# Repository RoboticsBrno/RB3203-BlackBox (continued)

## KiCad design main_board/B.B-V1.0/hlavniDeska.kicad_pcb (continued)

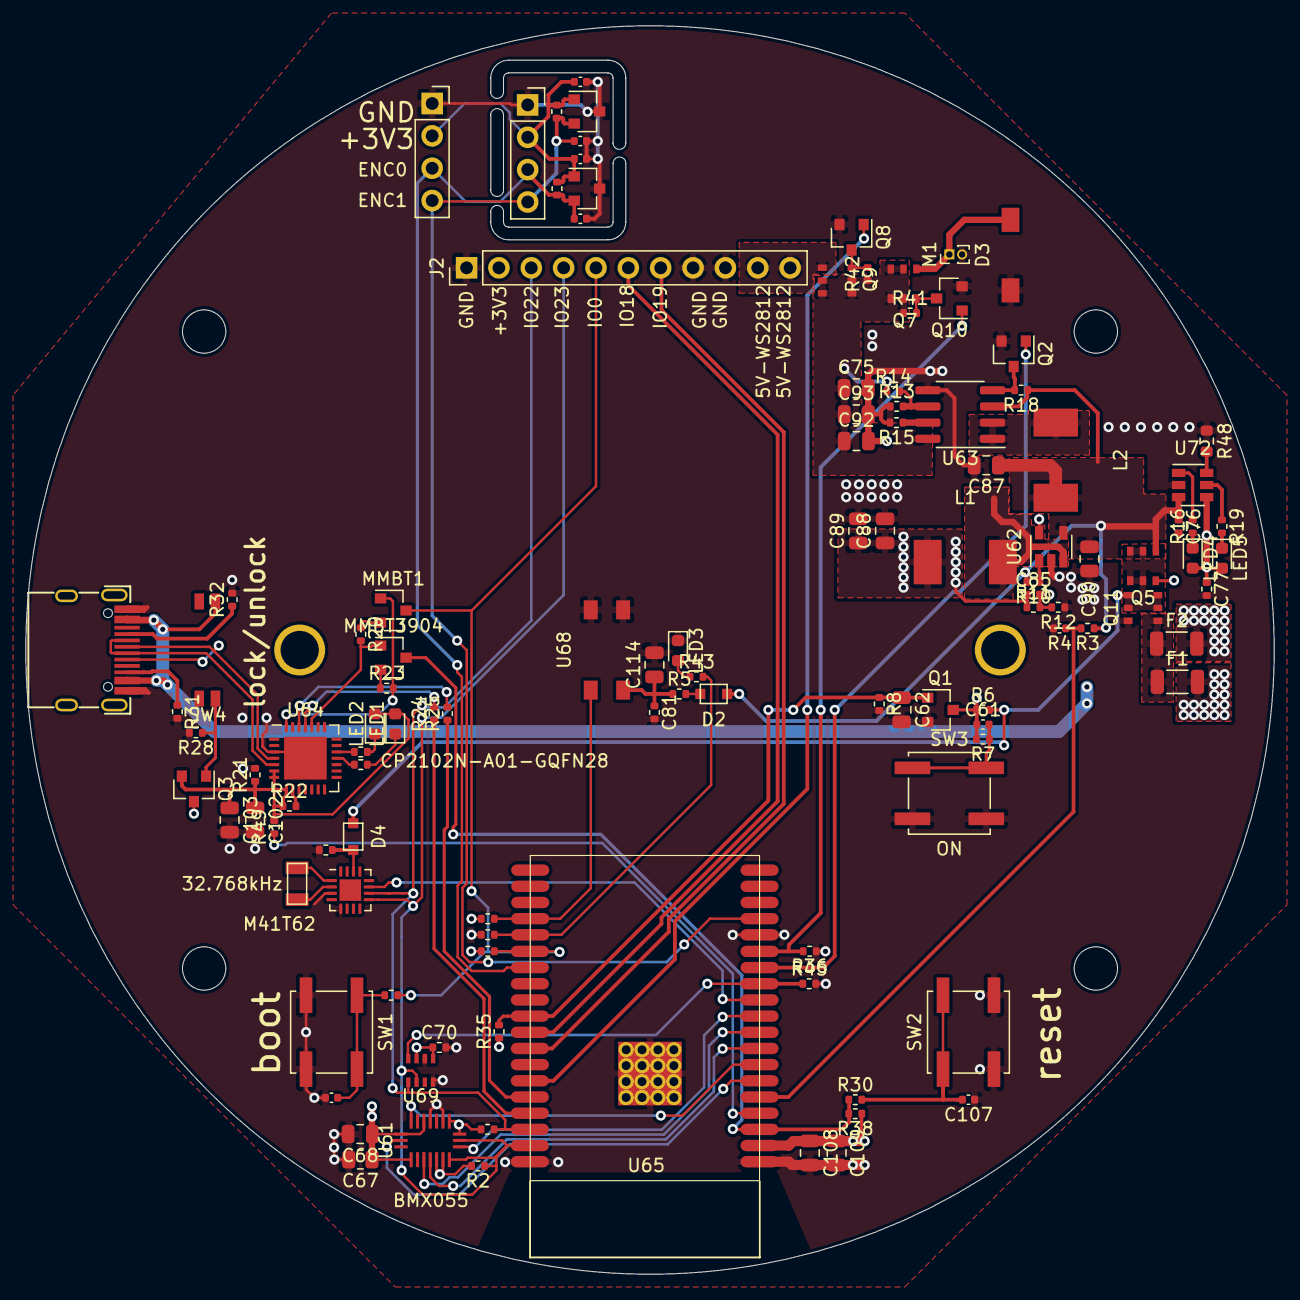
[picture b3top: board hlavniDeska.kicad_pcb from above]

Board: 4 copper layers, 98.0 x 98.0 mm, 117 parts (1 on the bottom side), 77 nets.

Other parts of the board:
C67: 10uf; R_0805_2012Metric
C68: 0.1uf; C_0805_2012Metric
C69, C70: 1uf; R_0402_1005Metric
D4: D; SOD-323
R45: 100k; R_0402_1005Metric
U61: BMX055; LGA_4.5x3
U67: M41T62; QFN-16-1EP_3x3mm_P0.5mm_EP1.7x1.7mm
U69: SPL06; SMD-8_2x2.5x0.65P
Y1: 32.768kHz; SMD-3215_2P

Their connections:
+3V3: C67.1, C68.1, C70.1, U61.3, U61.7, U61.12, U61.13, U61.17, U61.20, U69.6, U69.8; also elsewhere on the board
/BAT+: D4.2; also elsewhere on the board
/ESP3200/IO22: U67.10, U69.4; also elsewhere on the board
/ESP3200/IO23: U61.11, U67.9, U69.3; also elsewhere on the board
/ESP3200/IO25: U61.10; also elsewhere on the board
/ESP3200/IO26: U67.11; also elsewhere on the board
/ESP3200/IO27: R45.1, U69.5; also elsewhere on the board
/ESP3200/IO32: U61.14; also elsewhere on the board
/ESP3200/IO33: U61.15; also elsewhere on the board
/ESP3200/IO34: U61.19; also elsewhere on the board
/ESP3200/IO35: U61.1; also elsewhere on the board
GND: C67.2, C68.2, C69.2, C70.2, R45.2, U61.4, U61.6, U67.3, U67.5, U69.1, U69.7; also elsewhere on the board
unnamed: C69.1, D4.1, U67.14
unnamed: U67.1, Y1.1
unnamed: U67.2, Y1.2

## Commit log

2020-03-01 presun_do_solo_repozitare
2020-03-01 utrizeni
2020-10-04 LD_test
2020-10-06 KiCad-import
2020-10-27 New_B.B
    New schematic in KiCad.
    -ESP32 wrover
    + ESP32 have programer (CP3202) on board
    + CP3202 is consumed current only if USB is plug in
    -A9G
    + GPS, GPAR
2020-10-30 IR+ENC
2020-11-07 konzultace_s_Kubou_01
2020-11-07 pull_up(WS2812_power+motor)
2020-11-07 interrupt
    all interapt on PCA9555
2020-11-08 preparation_to_drawing_PCB
2020-11-09 complete_preparation_to_drawing_PCB
    footprint for all component and LCSC code for everything for mounting in JLCPCB
2020-11-09 repare last commit
    i forgot to save some footprint in last commit
2020-11-09 optimalizace_kondenzatoru
2020-11-12 start vith pcb
    firsxxt proposal component layout of main board
2020-11-15 orezavani
    smazaní A9G, SD karty, a zvuku
2020-11-17 nabijecka
2020-11-17 odpojovan_nabijecky
2020-11-21 18650
2020-11-28 polifuse
    -filtr k prijmaci IR
    -merwni bterky -> za zapinani
    -odstraneni odpojovani nabijecky + oprava napajeciho prouhu
    -odstraneni prevodniku napeti k WS2812
2020-11-28 PCB-0,1
2020-12-06 napajeni_na_stejne_strane
    -poradi na konektoru
    -napajeni IR prijmece z 5V na VCC
    -vyssi nabijeci proud
    -WS2812_power na IO21
2020-12-06 lenky_k_CP2102
2020-12-11 uvolneni enkoderu
    - dolomitelny enkoder
    - zmenseni via u civek LDC
    - vymena pouzdra USB-C
    - otoceni IR prijmace
    - zakas vylivani medi pod BMX9555
    - odstraneni "ochrannych" odporu k M41T62
2020-12-15 popisky
    -popisky
    -poladeni uddeleni enkoderu
    -poladeni nayvu drah
    -priopjeni gnd USB
    -poligon V5 na led-desce do spodni vrstvu
2020-12-16 LDC footprint
    prodlouzeni pedu pro usnadneni rucniho osazovani
2020-12-21 JLCdata
    - korekce pozice a natoceni
    - data pro vyrobu
2021-02-02 slozka_V1
2021-02-02 upravy_pouzder
2021-02-02 wrover
2021-02-02 opravi_a_dodatky MPU/QMC/conn_A9G
2021-02-02 podklady_a_modeli_3D_modelu
2021-04-07 opravy_a_dodatky_2
2021-05-18 lucerna
2021-05-19 posouvani-LCSC
2021-05-21 presuny_konektoru
2021-05-25 new schema
2021-05-25 spinana nabijecka a FT232 pcb
2021-05-26 vymena rezistoru pro snimani nabijeciho proudu
2021-06-21 touchboard-connectLed-isteni
2022-11-12 Outline schematic of the new lantern version
    Division into four PCB (PressPad , LEDBoard, MainBoard and bottom ServoButtonBoard)
    Equipmant:
    PressPad - NFC coil and LDC targets
    LEDBoard - 60 LEDs circle with output conector, LDC and his coil, NFC chip M24SR64
    MainBoard - ESP32 WROVER with CP2102 USB to UART convertor, PowerControler (two chargers TP5100 for charging four bateris 18650, linear regulator for 3V3 branch and stepup for 5V branch, main power s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
    ServoBoard - pin expander CY8C9520A and conectors
2023-03-16 Tests
2023-07-21 Establishment of the Kicadi Project
2023-07-21 clean
2023-07-23 Two 5V brange with automatic shutdown step-up
2023-07-23 Simplify of automatic shutdown step-up
2023-07-29 5V branch
